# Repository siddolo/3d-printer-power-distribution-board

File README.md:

# 3D Printer Power Distribution Board

This simple PCB is useful to distribute power to tools and accessories of 3D printer

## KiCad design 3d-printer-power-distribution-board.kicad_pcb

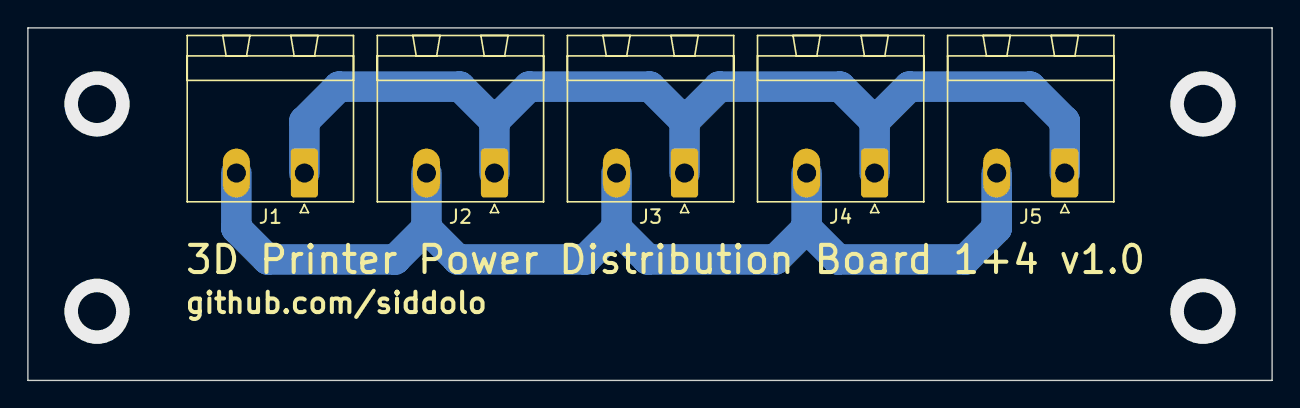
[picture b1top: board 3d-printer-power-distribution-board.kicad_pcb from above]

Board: 2 copper layers, 91.4 x 25.9 mm, 5 parts (0 on the bottom side), 2 nets.

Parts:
J1, J2, J3, J4, J5: Conn_01x02; PhoenixContact_MSTBA_2,5_2-G_1x02_P5.00mm_Horizontal

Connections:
unnamed: J1.1, J2.1, J3.1, J4.1, J5.1
unnamed: J1.2, J2.2, J3.2, J4.2, J5.2

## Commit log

2020-01-16 1st commit
2020-01-16 gerber
2020-12-10 photo
